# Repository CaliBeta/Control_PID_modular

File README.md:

# Control_PID_modular
Controlador PID analogo y digital para tres plantas de diferente respuesta. las ganancias se varían mediante potenciometros digitales

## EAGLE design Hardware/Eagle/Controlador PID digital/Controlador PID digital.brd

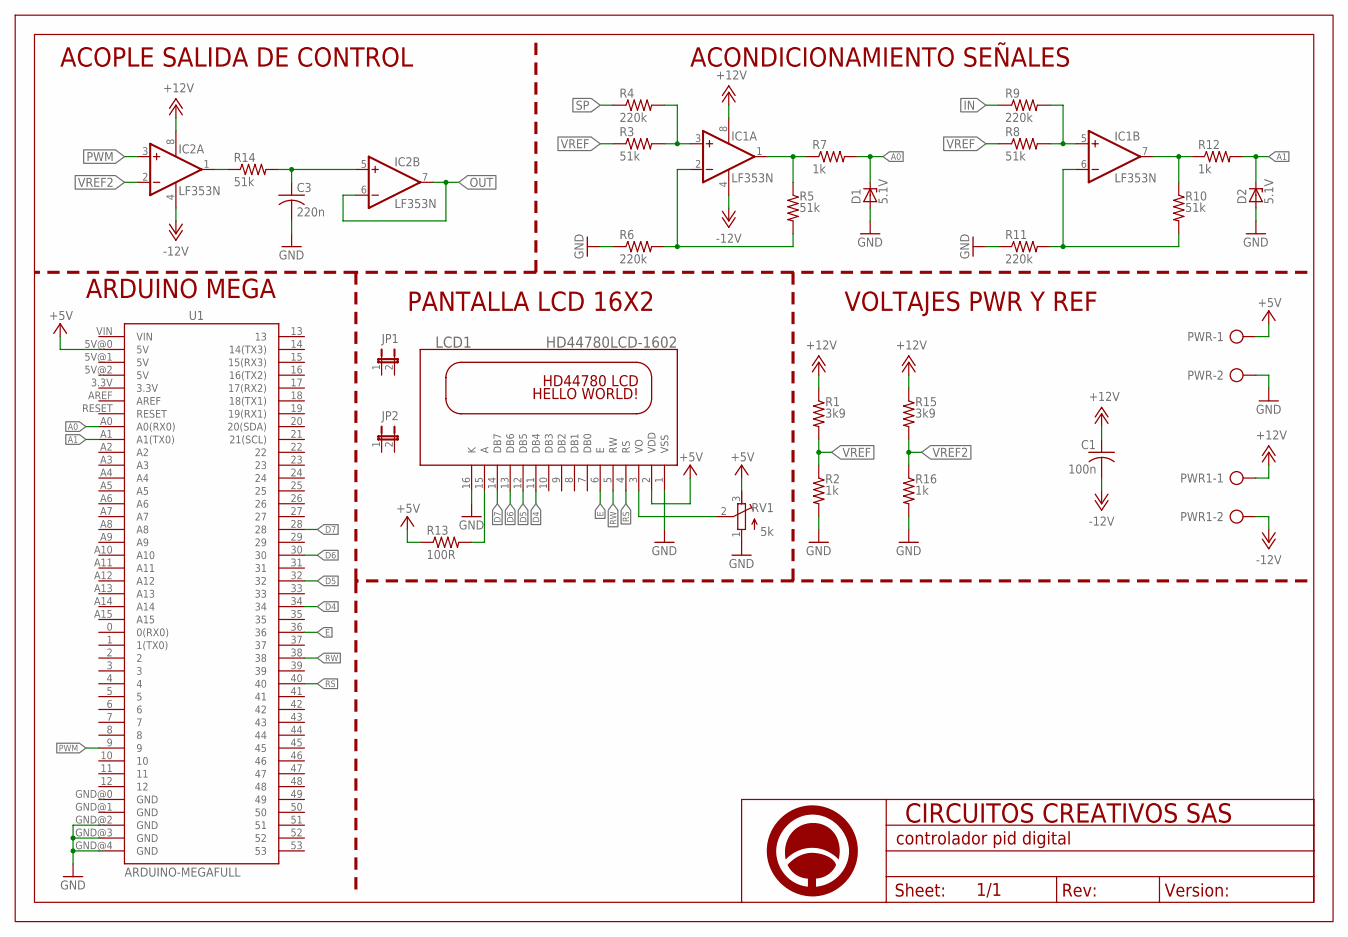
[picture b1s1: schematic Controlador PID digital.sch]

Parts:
C1: 100n; C025-025X050
C3: 220n; C050-030X075
D1, D2: 5.1V; DO41Z10
IC1, IC2: LF353N; DIL08
JP1, JP2: JP1E; JP1
LCD1: HD44780LCD-1602; LCD1602
PWR, PWR1: AK500/2
R1, R15: 3k9; 0204/7
R2, R7, R12, R16: 1k; 0204/7
R3, R5, R8, R10, R14: 51k; 0204/7
R4, R6, R9, R11: 220k; 0204/7
R13: 100R; 0204/7
RV1: 5k; RTRIM3296W
U1: ARDUINO-MEGAFULL; ARDUINO_MEGA
U$1: A4_HORIZONTAL; LOGO

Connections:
+5V: LCD1.2 (VDD), PWR.1, R13.1, RV1.3 (E), U1.5V@0 (5V)
+12V: C1.1, IC1.8 (V+), IC2.8 (V+), PWR1.1, R1.1, R15.1
-12V: C1.2, IC1.4 (V-), IC2.4 (V-), PWR1.2
A0: D1.C, R7.2, U1.A0 (A0(RX0))
A1: D2.C, R12.2, U1.A1 (A1(TX0))
D4: LCD1.11 (DB4), U1.34
D5: LCD1.12 (DB5), U1.32
D6: LCD1.13 (DB6), U1.30
D7: LCD1.14 (DB7), U1.28
E: LCD1.6 (E), U1.36
GND: C3.2, D1.A, D2.A, LCD1.1 (VSS), LCD1.16 (K), PWR.2, R2.2, R6.1, R11.1, R16.2, RV1.1 (A), U1.GND@2 (GND), U1.GND@3 (GND), U1.GND@4 (GND)
IN: R9.1
unnamed: IC1.5 (+IN), R8.2, R9.2
unnamed: IC1.2 (-IN), R5.2, R6.2
unnamed: IC1.6 (-IN), R10.2, R11.2
unnamed: IC1.3 (+IN), R3.2, R4.2
unnamed: IC1.1 (OUT), R5.1, R7.1
unnamed: IC1.7 (OUT), R10.1, R12.1
unnamed: IC2.1 (OUT), R14.1
unnamed: C3.1, IC2.5 (+IN), R14.2
unnamed: LCD1.3 (VO), RV1.2 (S)
unnamed: LCD1.15 (A), R13.2
OUT: IC2.6 (-IN), IC2.7 (OUT)
PWM: IC2.3 (+IN), U1.9
RS: LCD1.4 (RS), U1.40
RW: LCD1.5 (RW), U1.38
SP: R4.1
VREF: R1.2, R2.1, R3.1, R8.1
VREF2: IC2.2 (-IN), R15.2, R16.1

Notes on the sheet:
ACONDICIONAMIENTO SEÑALES
ACOPLE SALIDA DE CONTROL
ARDUINO MEGA
PANTALLA LCD 16X2
VOLTAJES PWR Y REF

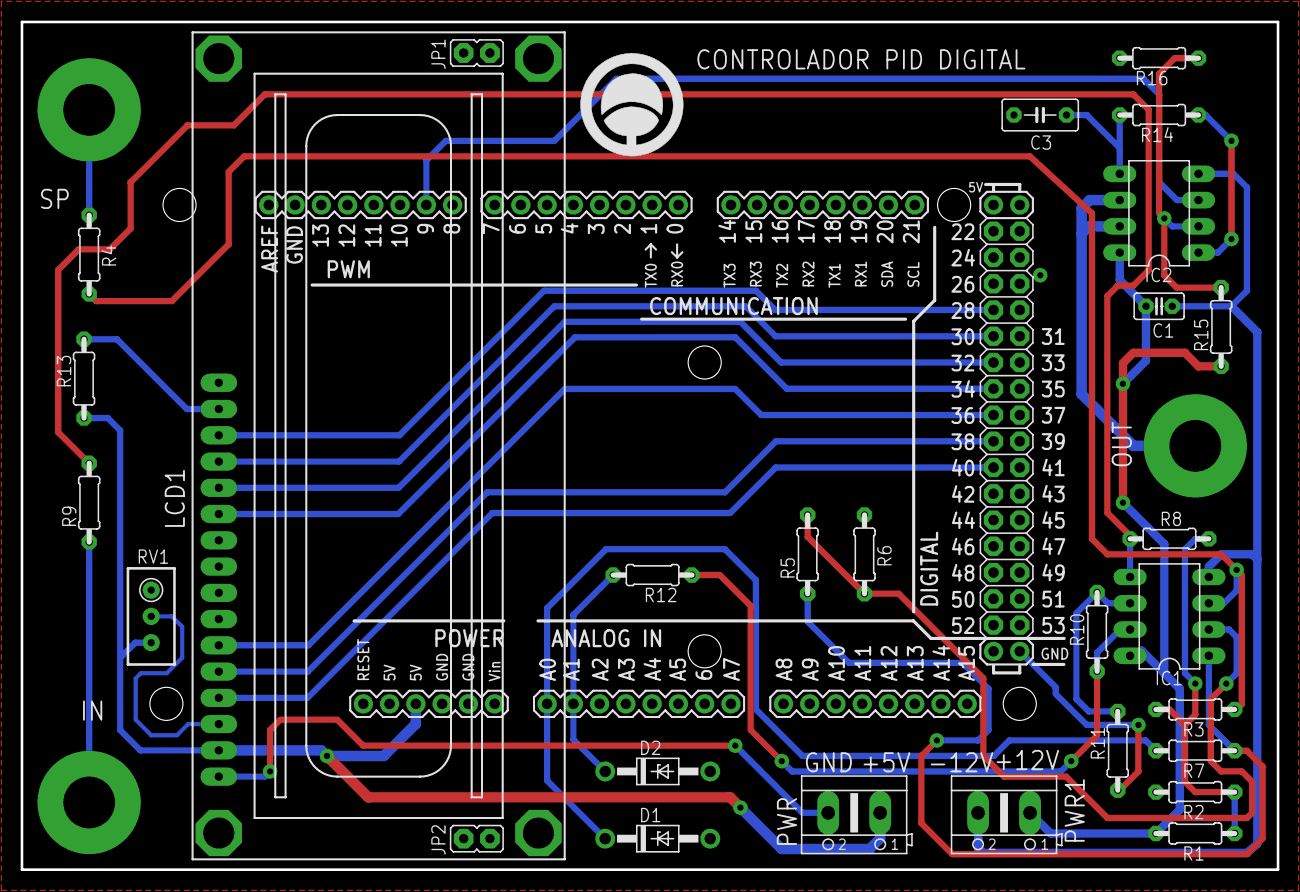
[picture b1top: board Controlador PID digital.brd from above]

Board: 2 copper layers, 121.5 x 82.0 mm, 30 parts (0 on the bottom side), 27 nets.

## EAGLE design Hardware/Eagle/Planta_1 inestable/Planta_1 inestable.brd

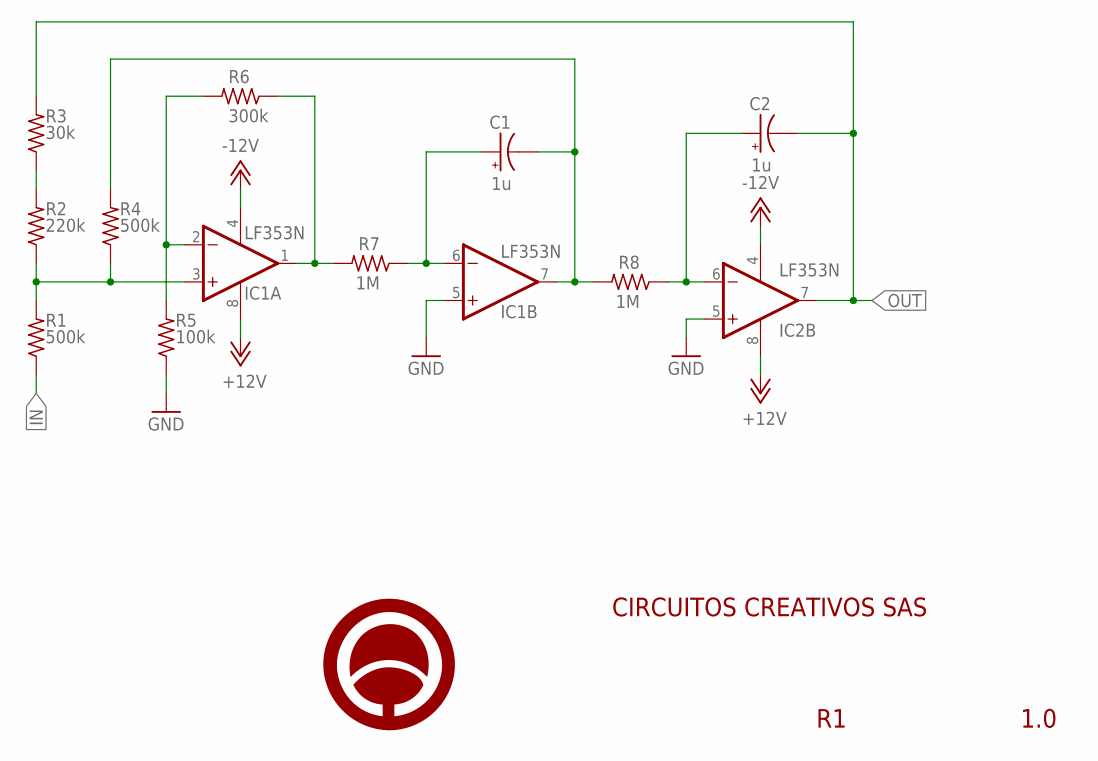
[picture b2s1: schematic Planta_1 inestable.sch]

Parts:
C1, C2: 1u; E2-5
IC1, IC2: LF353N; DIL08
R1, R4: 500k; 0204/7
R2: 220k; 0204/7
R3: 30k; 0204/7
R5: 100k; 0204/7
R6: 300k; 0204/7
R7, R8: 1M; 0204/7
U$1: LOGO

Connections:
+12V: IC1.8 (V+), IC2.8 (V+)
-12V: IC1.4 (V-), IC2.4 (V-)
GND: IC1.5 (+IN), IC2.5 (+IN), R5.1
IN: R1.1
unnamed: IC1.3 (+IN), R1.2, R2.1, R4.1
unnamed: R2.2, R3.1
unnamed: IC1.2 (-IN), R5.2, R6.2
unnamed: IC1.1 (OUT), R6.1, R7.2
unnamed: C1.+, IC1.6 (-IN), R7.1
unnamed: C1.-, IC1.7 (OUT), R4.2, R8.2
unnamed: C2.+, IC2.6 (-IN), R8.1
OUT: C2.-, IC2.7 (OUT), R3.2

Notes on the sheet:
CIRCUITOS CREATIVOS SAS
1.0

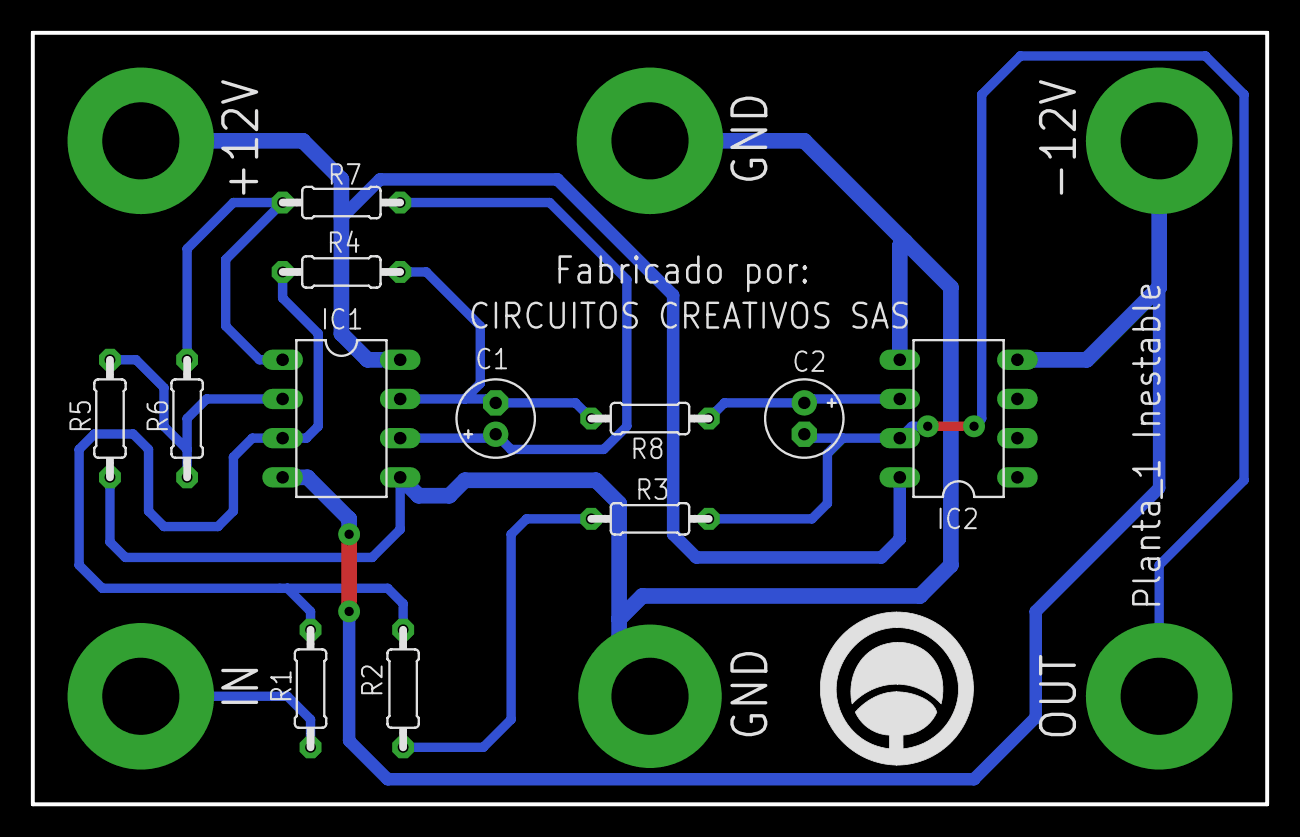
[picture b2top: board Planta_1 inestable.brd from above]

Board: 2 copper layers, 80.0 x 50.0 mm, 13 parts (0 on the bottom side), 11 nets.

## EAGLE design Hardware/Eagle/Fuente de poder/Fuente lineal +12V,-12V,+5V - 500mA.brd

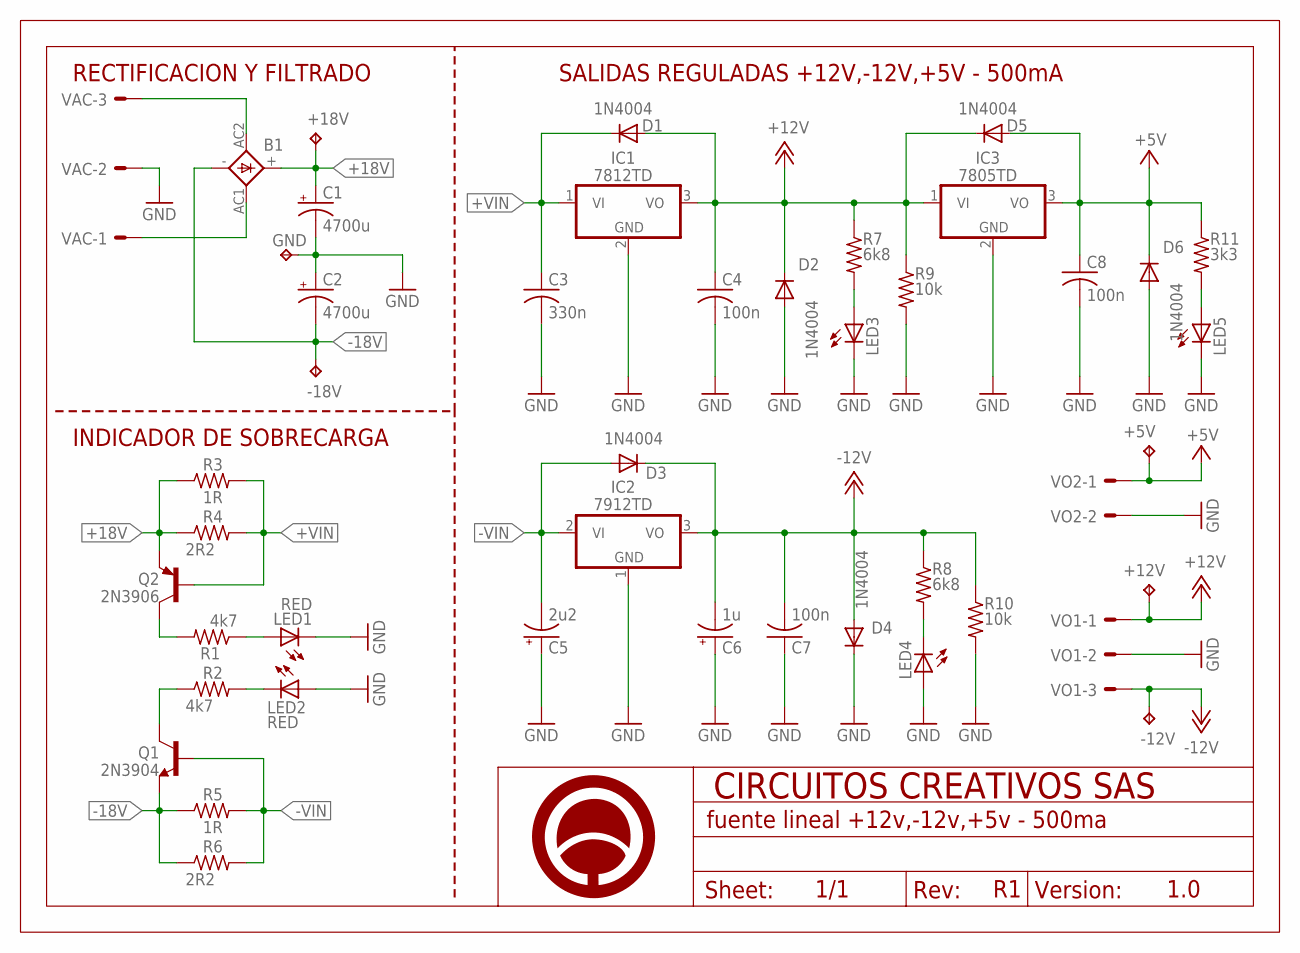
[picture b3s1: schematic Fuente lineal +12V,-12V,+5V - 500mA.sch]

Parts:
+5V, +12V, +18V: TPPAD1-17; P1-17
-12V, -18V: TPPAD1-17; P1-17
B1: KBL
C1, C2: 4700u; E7,5-16
C3: 330n; C050-030X075
C4, C7, C8: 100n; C050-030X075
C5: 2u2; E2,5-6E
C6: 1u; E2,5-6E
D1, D2, D3, D4, D5, D6: 1N4004; DO41-10
FRAME1: A5_HORIZONTAL; LOGO
GND: TPPAD1-17; P1-17
IC1: 7812TD; TO220VD
IC2: 7912TD; TO220VD
IC3: 7805TD; TO220VD
LED1, LED2: RED; LED5MM
LED3, LED4, LED5: LED5MM
Q1: 2N3904; TO-92
Q2: 2N3906; TO-92
R1, R2: 4k7; 0204/7
R3, R5: 1R; 0922/22
R4, R6: 2R2; 0922/22
R7, R8: 6k8; 0204/7
R9, R10: 10k; 0204/7
R11: 3k3; 0204/7
VAC: KK-156-3
VO1: KK-156-3
VO2: KK-156-2

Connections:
+5V: +5V.TP, C8.1, D5.A, D6.C, IC3.3 (VO), R11.1, VO2.1
+12V: +12V.TP, C4.1, D1.A, D2.C, D5.C, IC1.3 (VO), IC3.1 (VI), R7.1, R9.1, VO1.1
+18V: +18V.TP, B1.+, C1.+, Q2.1 (E), R3.1, R4.1
+VIN: C3.1, D1.C, IC1.1 (VI), Q2.2 (B), R3.2, R4.2
-12V: -12V.TP, C6.-, C7.2, D3.C, D4.A, IC2.3 (VO), R8.1, R10.1, VO1.3
-18V: -18V.TP, B1.-, C2.-, Q1.1 (E), R5.1, R6.1
-VIN: C5.-, D3.A, IC2.2 (VI), Q1.2 (B), R5.2, R6.2
GND: C1.-, C2.+, C3.2, C4.2, C5.+, C6.+, C7.1, C8.2, D2.A, D4.C, D6.A, GND.TP, IC1.2 (GND), IC2.1 (GND), IC3.2 (GND), LED1.K (C), LED2.A, LED3.K (C), LED4.A, LED5.K (C), R9.2, R10.2, VAC.2, VO1.2, VO2.2
unnamed: B1.AC2 (AC1), VAC.3
unnamed: B1.AC1 (AC2), VAC.1
unnamed: Q2.3 (C), R1.2
unnamed: LED4.K (C), R8.2
unnamed: Q1.3 (C), R2.1
unnamed: LED3.A, R7.2
unnamed: LED5.A, R11.2
unnamed: LED1.A, R1.1
unnamed: LED2.K (C), R2.2

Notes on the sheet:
RECTIFICACION Y FILTRADO
INDICADOR DE SOBRECARGA
1.0
SALIDAS REGULADAS +12V,-12V,+5V - 500mA

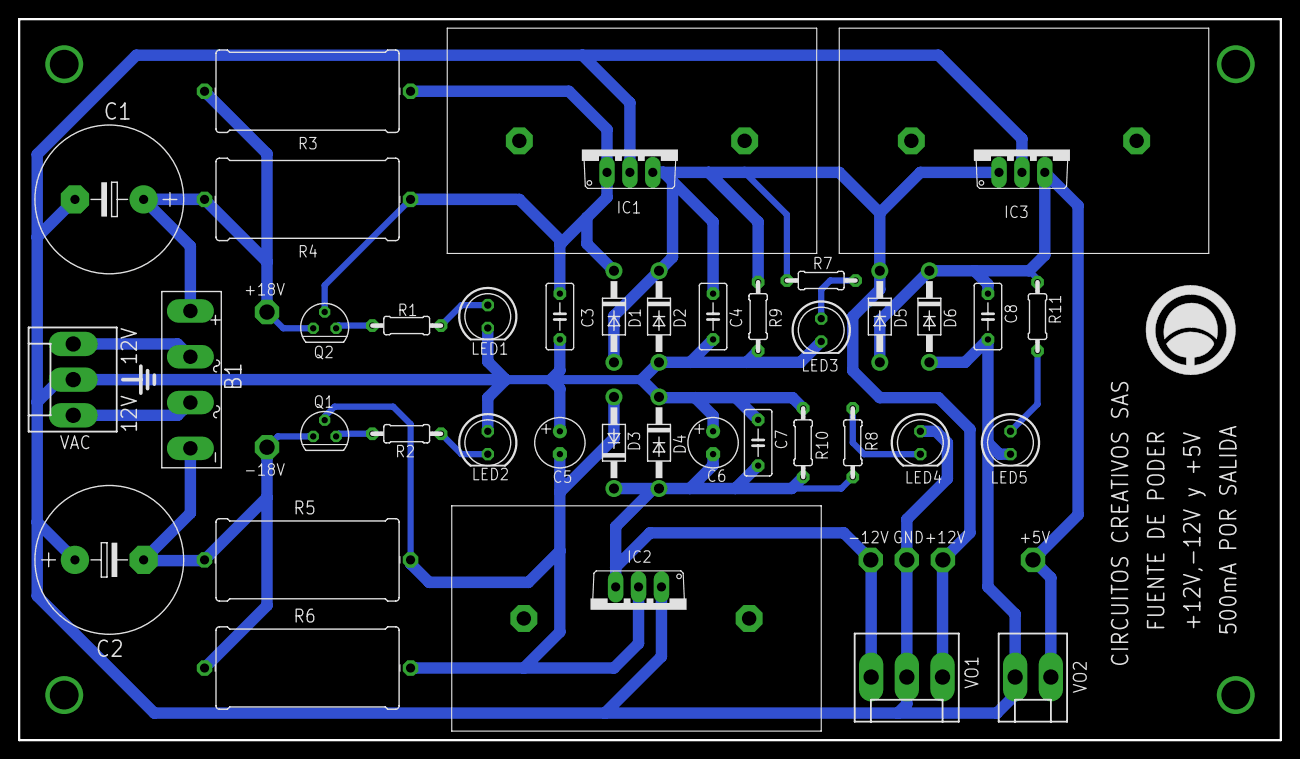
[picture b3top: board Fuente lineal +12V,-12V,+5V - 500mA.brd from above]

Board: 2 copper layers, 140.0 x 80.0 mm, 46 parts (0 on the bottom side), 17 nets.

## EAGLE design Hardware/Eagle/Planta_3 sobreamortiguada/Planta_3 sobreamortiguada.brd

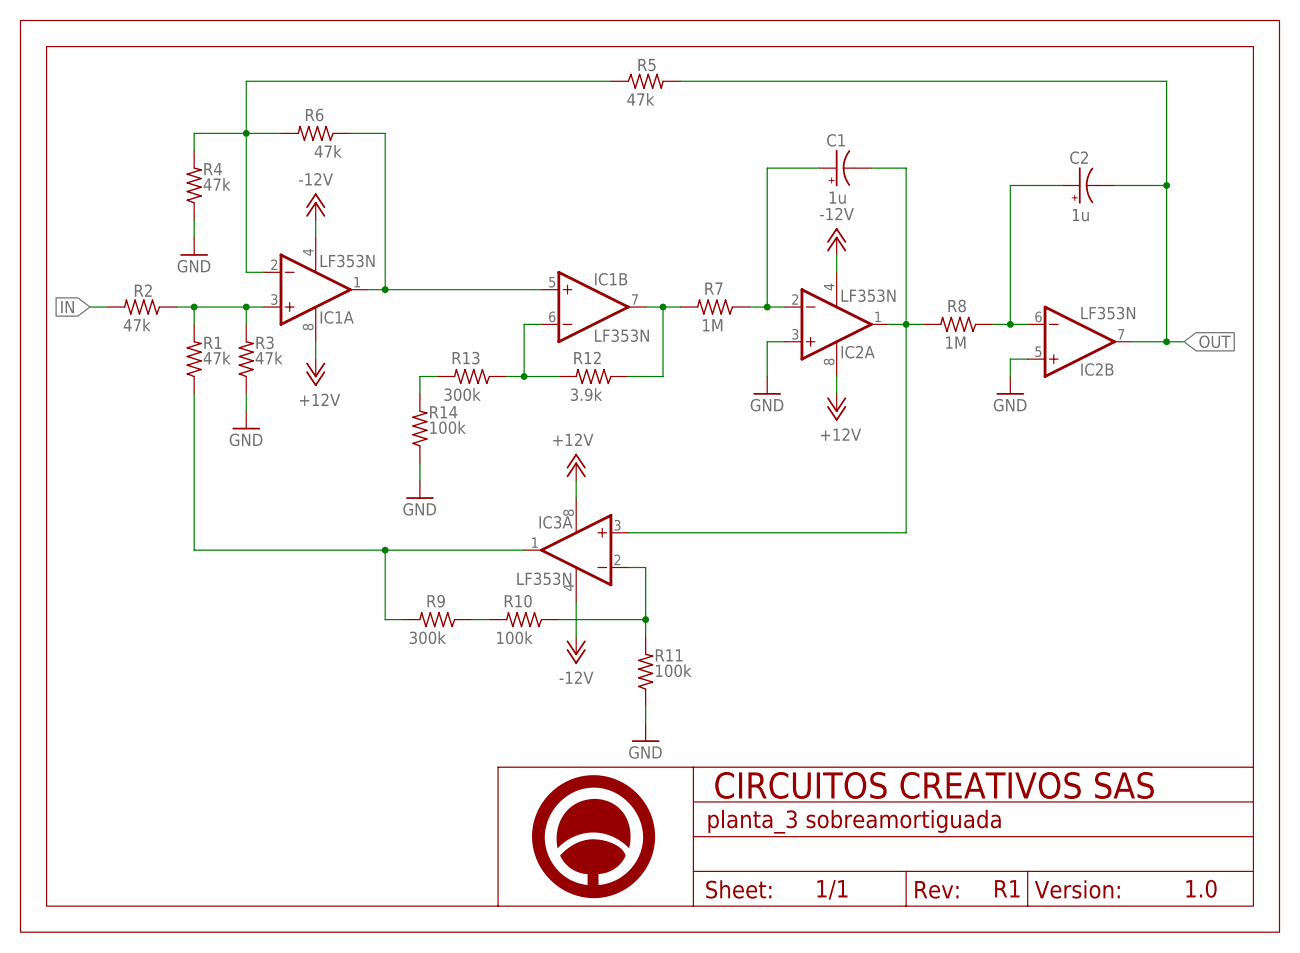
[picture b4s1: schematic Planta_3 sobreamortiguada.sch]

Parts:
C1, C2: 1u; E2-5
F1: A5_HORIZONTAL; LOGO
IC1, IC2, IC3: LF353N; DIL08
R1, R2, R3, R4, R5, R6: 47k; 0204/7
R7, R8: 1M; 0204/7
R9, R13: 300k; 0204/7
R10, R11, R14: 100k; 0204/7
R12: 3.9k; 0204/7

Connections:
+12V: IC1.8 (V+), IC2.8 (V+), IC3.8 (V+)
-12V: IC1.4 (V-), IC2.4 (V-), IC3.4 (V-)
GND: IC2.3 (+IN), IC2.5 (+IN), R3.1, R4.1, R11.1, R14.1
IN: R2.2
unnamed: IC1.2 (-IN), R4.2, R5.1, R6.2
unnamed: IC1.1 (OUT), IC1.5 (+IN), R6.1
unnamed: C1.+, IC2.2 (-IN), R7.1
unnamed: C1.-, IC2.1 (OUT), IC3.3 (+IN), R8.2
unnamed: C2.+, IC2.6 (-IN), R8.1
unnamed: R9.1, R10.2
unnamed: IC3.1 (OUT), R1.1, R9.2
unnamed: IC3.2 (-IN), R10.1, R11.2
unnamed: IC1.6 (-IN), R12.2, R13.1
unnamed: IC1.7 (OUT), R7.2, R12.1
unnamed: R13.2, R14.2
unnamed: IC1.3 (+IN), R1.2, R2.1, R3.2
OUT: C2.-, IC2.7 (OUT), R5.2

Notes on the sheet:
1.0

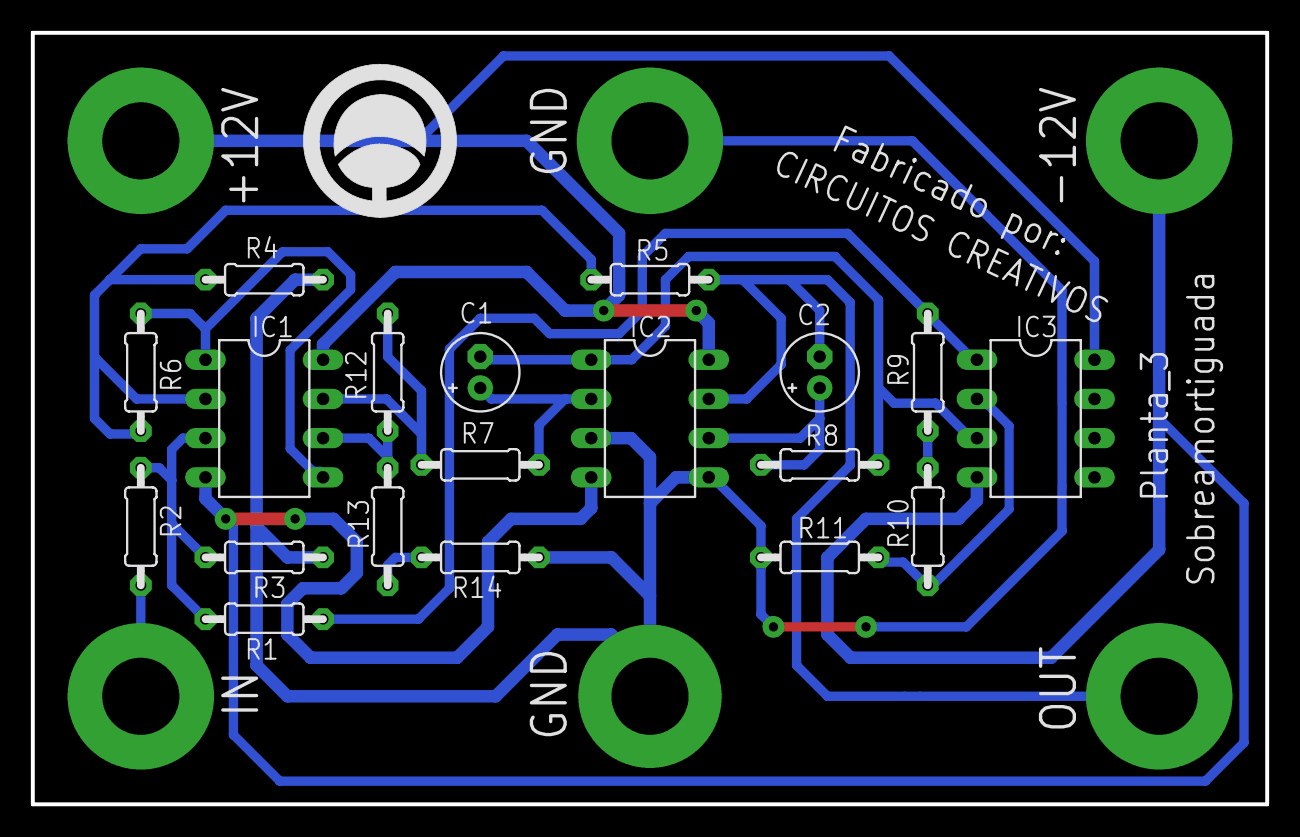
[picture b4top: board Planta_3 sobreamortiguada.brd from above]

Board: 2 copper layers, 80.0 x 50.0 mm, 20 parts (0 on the bottom side), 16 nets.

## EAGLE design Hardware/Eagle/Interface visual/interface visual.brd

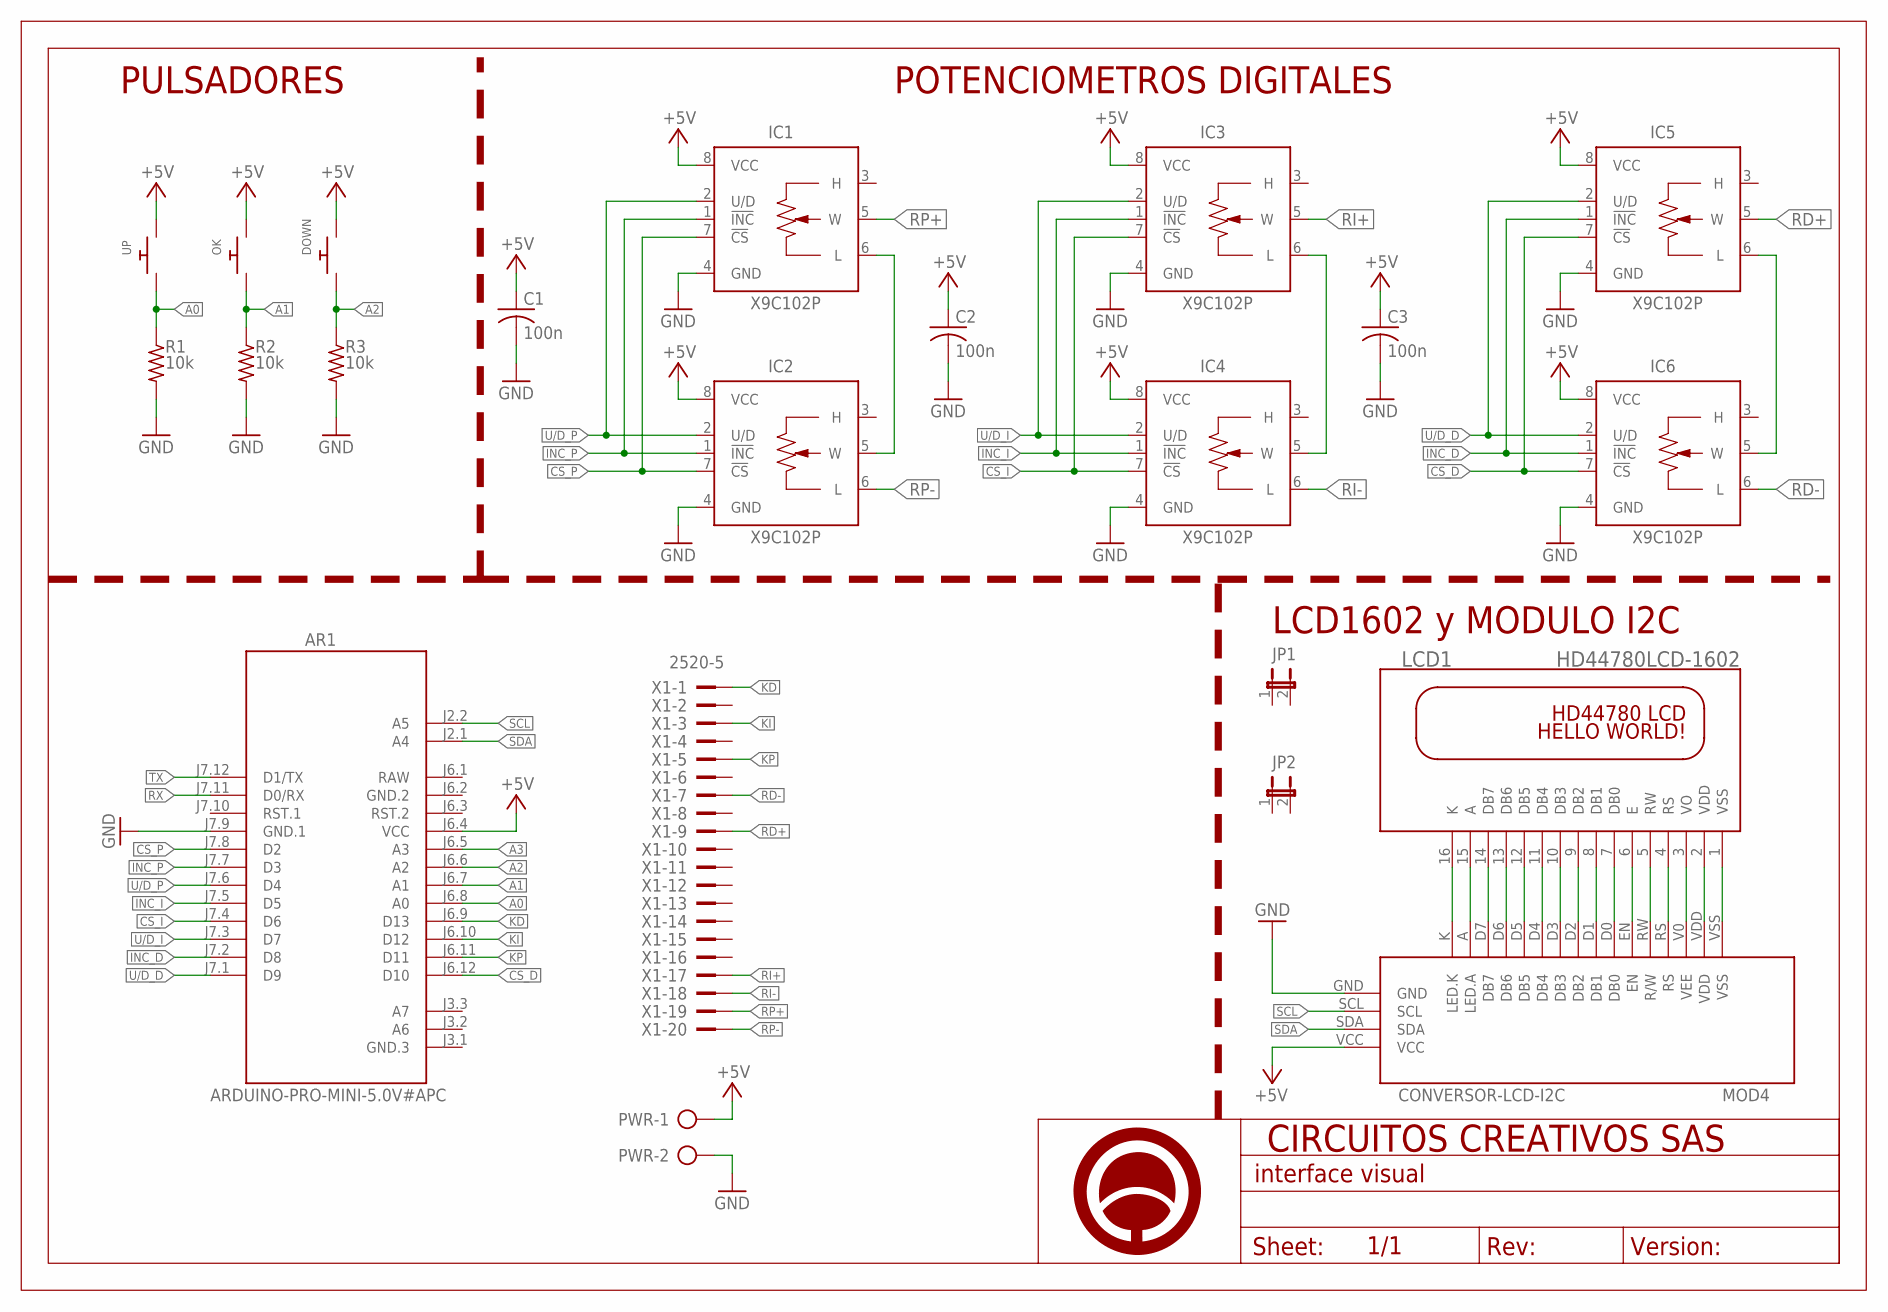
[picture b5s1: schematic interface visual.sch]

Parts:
AR1: ARDUINO-PRO-MINI-5.0V#APC; ARDUINO-PRO-MINI#APC
C1, C2, C3: 100n; C025-025X050
DOWN: SWITCH_PUSHBUTTONEVQ-PE; TACT_PANA-EVQ
IC1, IC2, IC3, IC4, IC5, IC6: X9C102P; DIL08
JP1, JP2: JP1E; JP1
LCD1: HD44780LCD-1602; LCD1602
MOD4: CONVERSOR-LCD-I2C
OK: SWITCH_PUSHBUTTONEVQ-PE; TACT_PANA-EVQ
PWR: AK500/2
R1, R2, R3: 10k; 0204/7
U$1: A4_HORIZONTAL; LOGO
UP: SWITCH_PUSHBUTTONEVQ-PE; TACT_PANA-EVQ
X1: 2520-5; PAK100/2500-5-20

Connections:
+5V: AR1.J6.4 (VCC), C1.1, C2.1, C3.1, DOWN.P$2, IC1.8 (VCC), IC2.8 (VCC), IC3.8 (VCC), IC4.8 (VCC), IC5.8 (VCC), IC6.8 (VCC), MOD4.VCC, OK.P$2, PWR.1, UP.P$2
A0: AR1.J6.8 (A0), R1.1, UP.P$1
A1: AR1.J6.7 (A1), OK.P$1, R2.1
A2: AR1.J6.6 (A2), DOWN.P$1, R3.1
A3: AR1.J6.5 (A3)
CS_D: AR1.J6.12 (D10), IC5.7 (!CS), IC6.7 (!CS)
CS_I: AR1.J7.4 (D6), IC3.7 (!CS), IC4.7 (!CS)
CS_P: AR1.J7.8 (D2), IC1.7 (!CS), IC2.7 (!CS)
GND: AR1.J7.9 (GND.1), C1.2, C2.2, C3.2, IC1.4 (GND), IC2.4 (GND), IC3.4 (GND), IC4.4 (GND), IC5.4 (GND), IC6.4 (GND), MOD4.GND, PWR.2, R1.2, R2.2, R3.2
GND.2: AR1.J6.2 (GND.2)
INC_D: AR1.J7.2 (D8), IC5.1 (!INC), IC6.1 (!INC)
INC_I: AR1.J7.5 (D5), IC3.1 (!INC), IC4.1 (!INC)
INC_P: AR1.J7.7 (D3), IC1.1 (!INC), IC2.1 (!INC)
KD: AR1.J6.9 (D13), X1.1
KI: AR1.J6.10 (D12), X1.3
KP: AR1.J6.11 (D11), X1.5
unnamed: IC3.6 (L), IC4.5 (W)
unnamed: IC1.6 (L), IC2.5 (W)
unnamed: IC5.6 (L), IC6.5 (W)
unnamed: LCD1.3 (VO), MOD4.V0 (VEE)
unnamed: LCD1.4 (RS), MOD4.RS
unnamed: LCD1.5 (RW), MOD4.RW (R/W)
unnamed: LCD1.7 (DB0), MOD4.D0 (DB0)
unnamed: LCD1.6 (E), MOD4.EN
unnamed: LCD1.8 (DB1), MOD4.D1 (DB1)
unnamed: LCD1.9 (DB2), MOD4.D2 (DB2)
unnamed: LCD1.10 (DB3), MOD4.D3 (DB3)
unnamed: LCD1.11 (DB4), MOD4.D4 (DB4)
unnamed: LCD1.12 (DB5), MOD4.D5 (DB5)
unnamed: LCD1.13 (DB6), MOD4.D6 (DB6)
unnamed: LCD1.14 (DB7), MOD4.D7 (DB7)
unnamed: LCD1.15 (A), MOD4.A (LED.A)
unnamed: LCD1.16 (K), MOD4.K (LED.K)
RAW: AR1.J6.1 (RAW)
RD+: IC5.5 (W), X1.9
RD-: IC6.6 (L), X1.7
RI+: IC3.5 (W), X1.17
RI-: IC4.6 (L), X1.18
RP+: IC1.5 (W), X1.19
RP-: IC2.6 (L), X1.20
RX: AR1.J7.11 (D0/RX)
SCL: AR1.J2.2 (A5), MOD4.SCL
SDA: AR1.J2.1 (A4), MOD4.SDA
TX: AR1.J7.12 (D1/TX)
U/D_D: AR1.J7.1 (D9), IC5.2 (U/D), IC6.2 (U/D)
U/D_I: AR1.J7.3 (D7), IC3.2 (U/D), IC4.2 (U/D)
U/D_P: AR1.J7.6 (D4), IC1.2 (U/D), IC2.2 (U/D)
VDD: LCD1.2 (VDD), MOD4.VDD
VSS: LCD1.1 (VSS), MOD4.VSS

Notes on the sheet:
LCD1602 y MODULO I2C
POTENCIOMETROS DIGITALES
PULSADORES

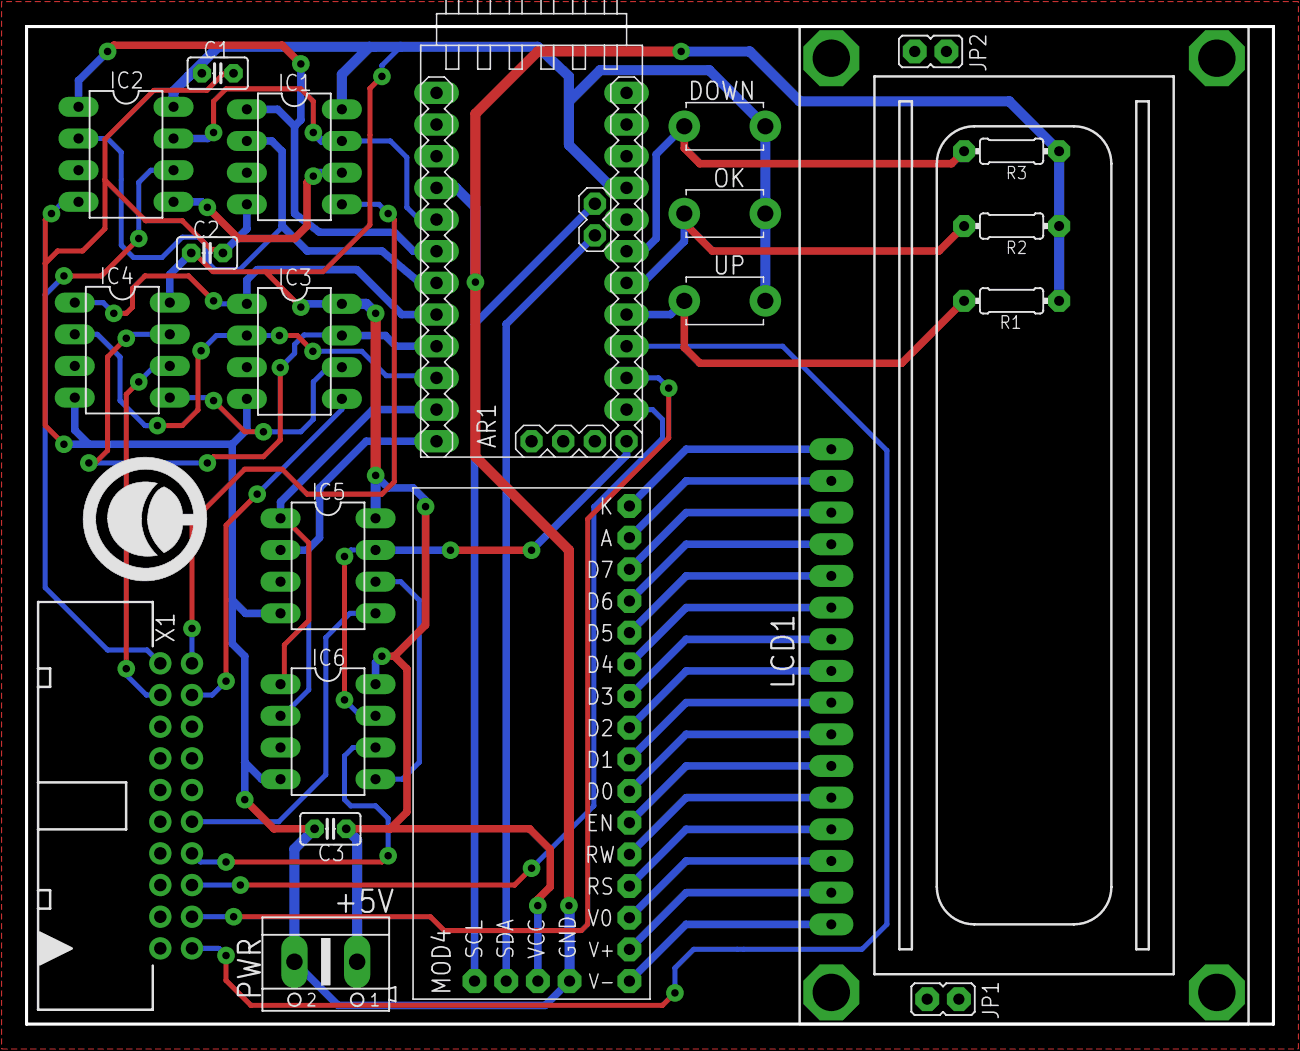
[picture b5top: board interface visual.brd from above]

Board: 2 copper layers, 100.0 x 80.0 mm, 23 parts (0 on the bottom side), 44 nets.

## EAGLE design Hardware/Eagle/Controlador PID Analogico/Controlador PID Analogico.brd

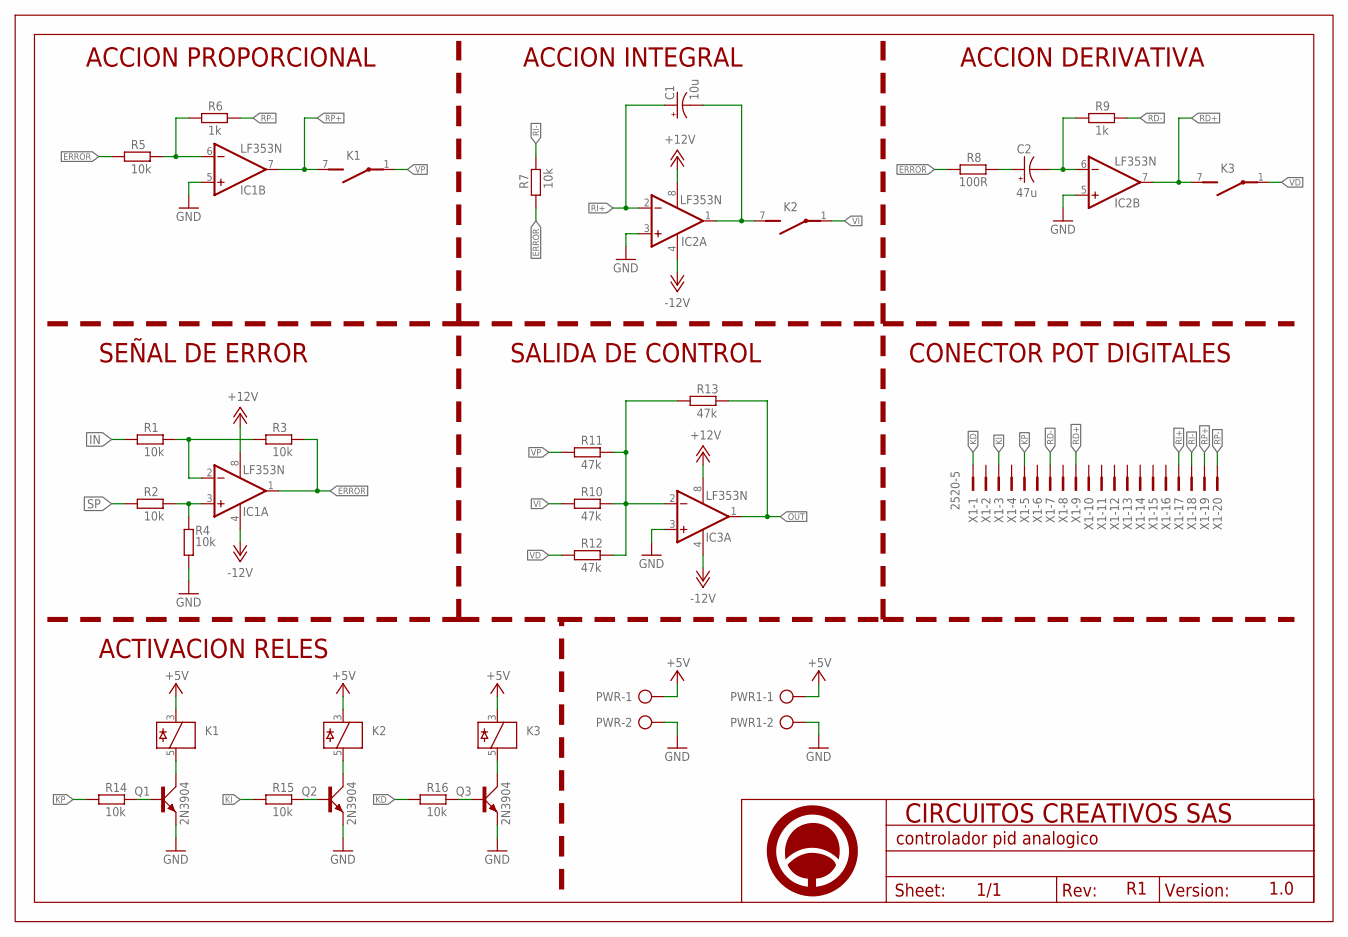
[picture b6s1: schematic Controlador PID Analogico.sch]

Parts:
C1: 10u; E2,5-6E
C2: 47u; E2,5-6E
IC1, IC2, IC3: LF353N; DIL08
K1, K2, K3: 35701331; REED
PWR, PWR1: AK500/2
Q1, Q2, Q3: 2N3904; TO92D
R1, R2, R3, R4, R5, R7, R14, R15, R16: 10k; 0204/7
R6, R9: 1k; 0204/7
R8: 100R; 0204/7
R10, R11, R12, R13: 47k; 0204/7
U$1: A4_HORIZONTAL; LOGO
X1: 2520-5; PAK100/2500-5-20

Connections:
+5V: K1.3, K2.3, K3.3, PWR.1, PWR1.1
+12V: IC1.8 (V+), IC2.8 (V+), IC3.8 (V+)
-12V: IC1.4 (V-), IC2.4 (V-), IC3.4 (V-)
ERROR: IC1.1 (OUT), R3.2, R5.2, R7.2, R8.1
GND: IC1.5 (+IN), IC2.3 (+IN), IC2.5 (+IN), IC3.3 (+IN), PWR.2, PWR1.2, Q1.E, Q2.E, Q3.E, R4.2
IN: R1.1
KD: R16.1, X1.1
KI: R15.1, X1.3
KP: R14.1, X1.5
unnamed: IC1.2 (-IN), R1.2, R3.1
unnamed: IC1.3 (+IN), R2.2, R4.1
unnamed: IC1.6 (-IN), R5.1, R6.1
unnamed: C1.-, IC2.1 (OUT), K2.7 (S)
unnamed: C2.-, IC2.6 (-IN), R9.1
unnamed: C2.+, R8.2
unnamed: IC3.2 (-IN), R10.2, R11.2, R12.2, R13.1
unnamed: Q1.B, R14.2
unnamed: K1.5, Q1.C
unnamed: Q2.B, R15.2
unnamed: K2.5, Q2.C
unnamed: Q3.B, R16.2
unnamed: K3.5, Q3.C
OUT: IC3.1 (OUT), R13.2
RD+: IC2.7 (OUT), K3.7 (S), X1.9
RD-: R9.2, X1.7
RI+: C1.+, IC2.2 (-IN), X1.17
RI-: R7.1, X1.18
RP+: IC1.7 (OUT), K1.7 (S), X1.19
RP-: R6.2, X1.20
SP: R2.1
VD: K3.1, R12.1
VI: K2.1, R10.1
VP: K1.1, R11.1

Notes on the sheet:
1.0
ACCION PROPORCIONAL
ACCION INTEGRAL
ACCION DERIVATIVA
SEÑAL DE ERROR
SALIDA DE CONTROL
ACTIVACION RELES
CONECTOR POT DIGITALES

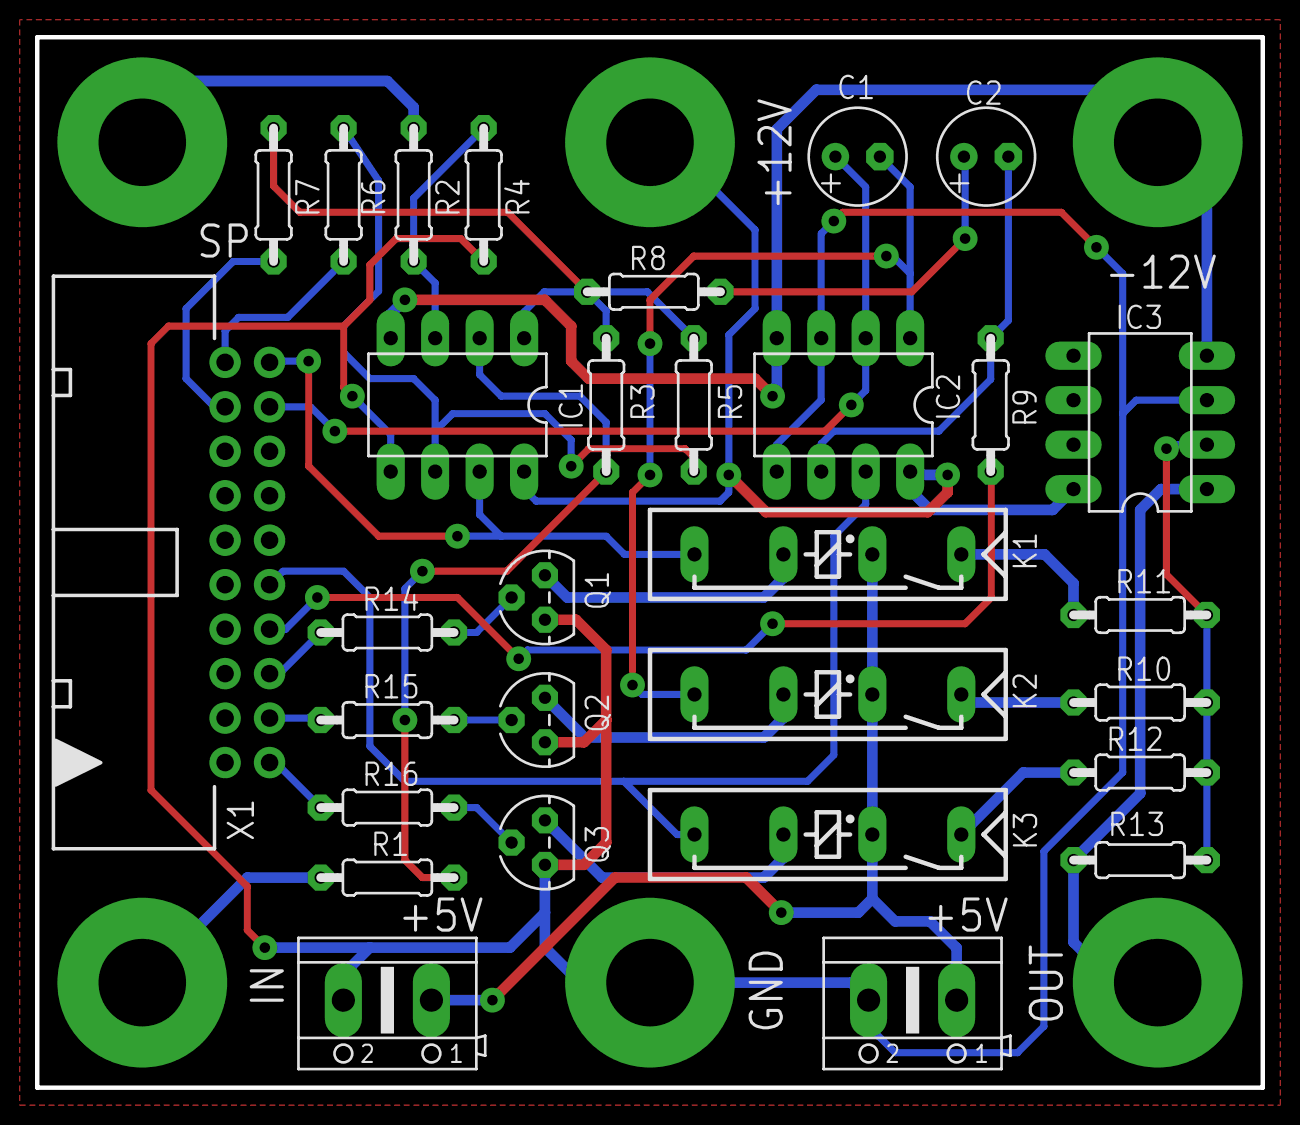
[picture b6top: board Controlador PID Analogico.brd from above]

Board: 2 copper layers, 70.0 x 60.0 mm, 31 parts (1 on the bottom side), 31 nets.

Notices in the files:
parts and their libraries:
SparkFun-Boards: Licensing: Creative Commons ShareAlike 4.0 International - https://creativecommons.org/licenses/by-sa/4.0
DIY- comercial modules: Released under the Creative Commons Attribution 4.0 International License: http://creativecommons.org/licenses/by/4.0
